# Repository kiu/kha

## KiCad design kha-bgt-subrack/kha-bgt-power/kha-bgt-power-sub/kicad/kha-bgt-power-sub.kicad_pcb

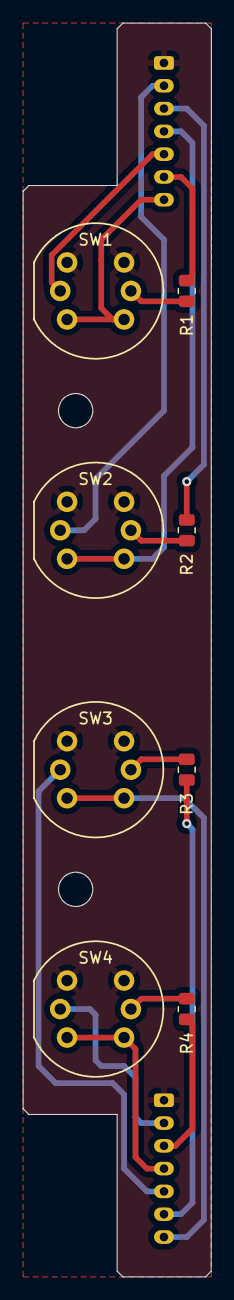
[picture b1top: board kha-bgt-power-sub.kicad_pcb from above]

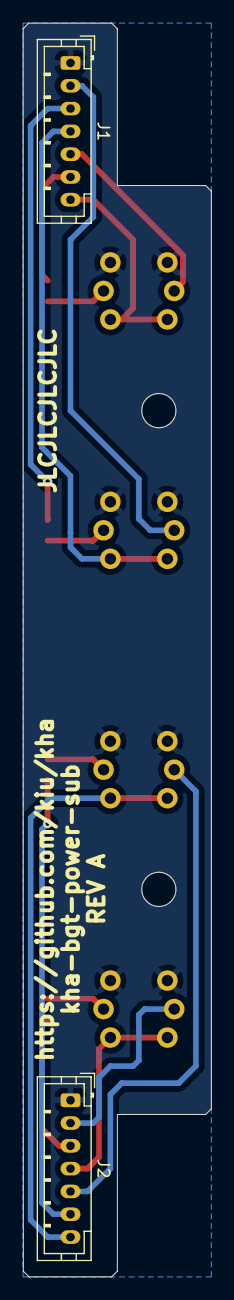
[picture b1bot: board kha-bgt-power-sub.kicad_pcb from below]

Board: 2 copper layers, 16.5 x 110.0 mm, 10 parts (2 on the bottom side), 17 nets.

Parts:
J1, J2: Conn_01x07; JST_PH_B7B-PH-K_1x07_P2.00mm_Vertical
R1, R2, R3, R4: R; R_0805_2012Metric
SW1, SW2, SW3, SW4: KS01-BL

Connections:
GND: J1.1, J2.1, SW1.2, SW2.2, SW3.2, SW4.2
unnamed: J1.2, SW2.6
unnamed: J1.3, R2.1
unnamed: J1.4, SW2.1
unnamed: J1.5, SW1.6
unnamed: J1.6, R1.1
unnamed: J1.7, SW1.1
unnamed: J2.2, SW4.6
unnamed: J2.3, R4.1
unnamed: J2.4, SW4.1
unnamed: J2.5, SW3.6
unnamed: J2.6, R3.1
unnamed: J2.7, SW3.1
unnamed: R1.2, SW1.5
unnamed: R2.2, SW2.5
unnamed: R3.2, SW3.5
unnamed: R4.2, SW4.5
